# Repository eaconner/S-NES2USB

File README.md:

# (S)NES2USB

Upgrade your NES or SNES controller to USB. Can be put inside the controller, or build real NES/SNES ports onto your computer. Works with standard controllers (original, Max, dogbone, Advantage, etc), does not work with peripherals (Zapper, FourScore, etc).
[OSHPark](https://oshpark.com/shared_projects/MCnz0W9w)  |  [DigiKey BOM](https://www.digikey.com/BOM/Create/CreateSharedBom?bomId=7739089)

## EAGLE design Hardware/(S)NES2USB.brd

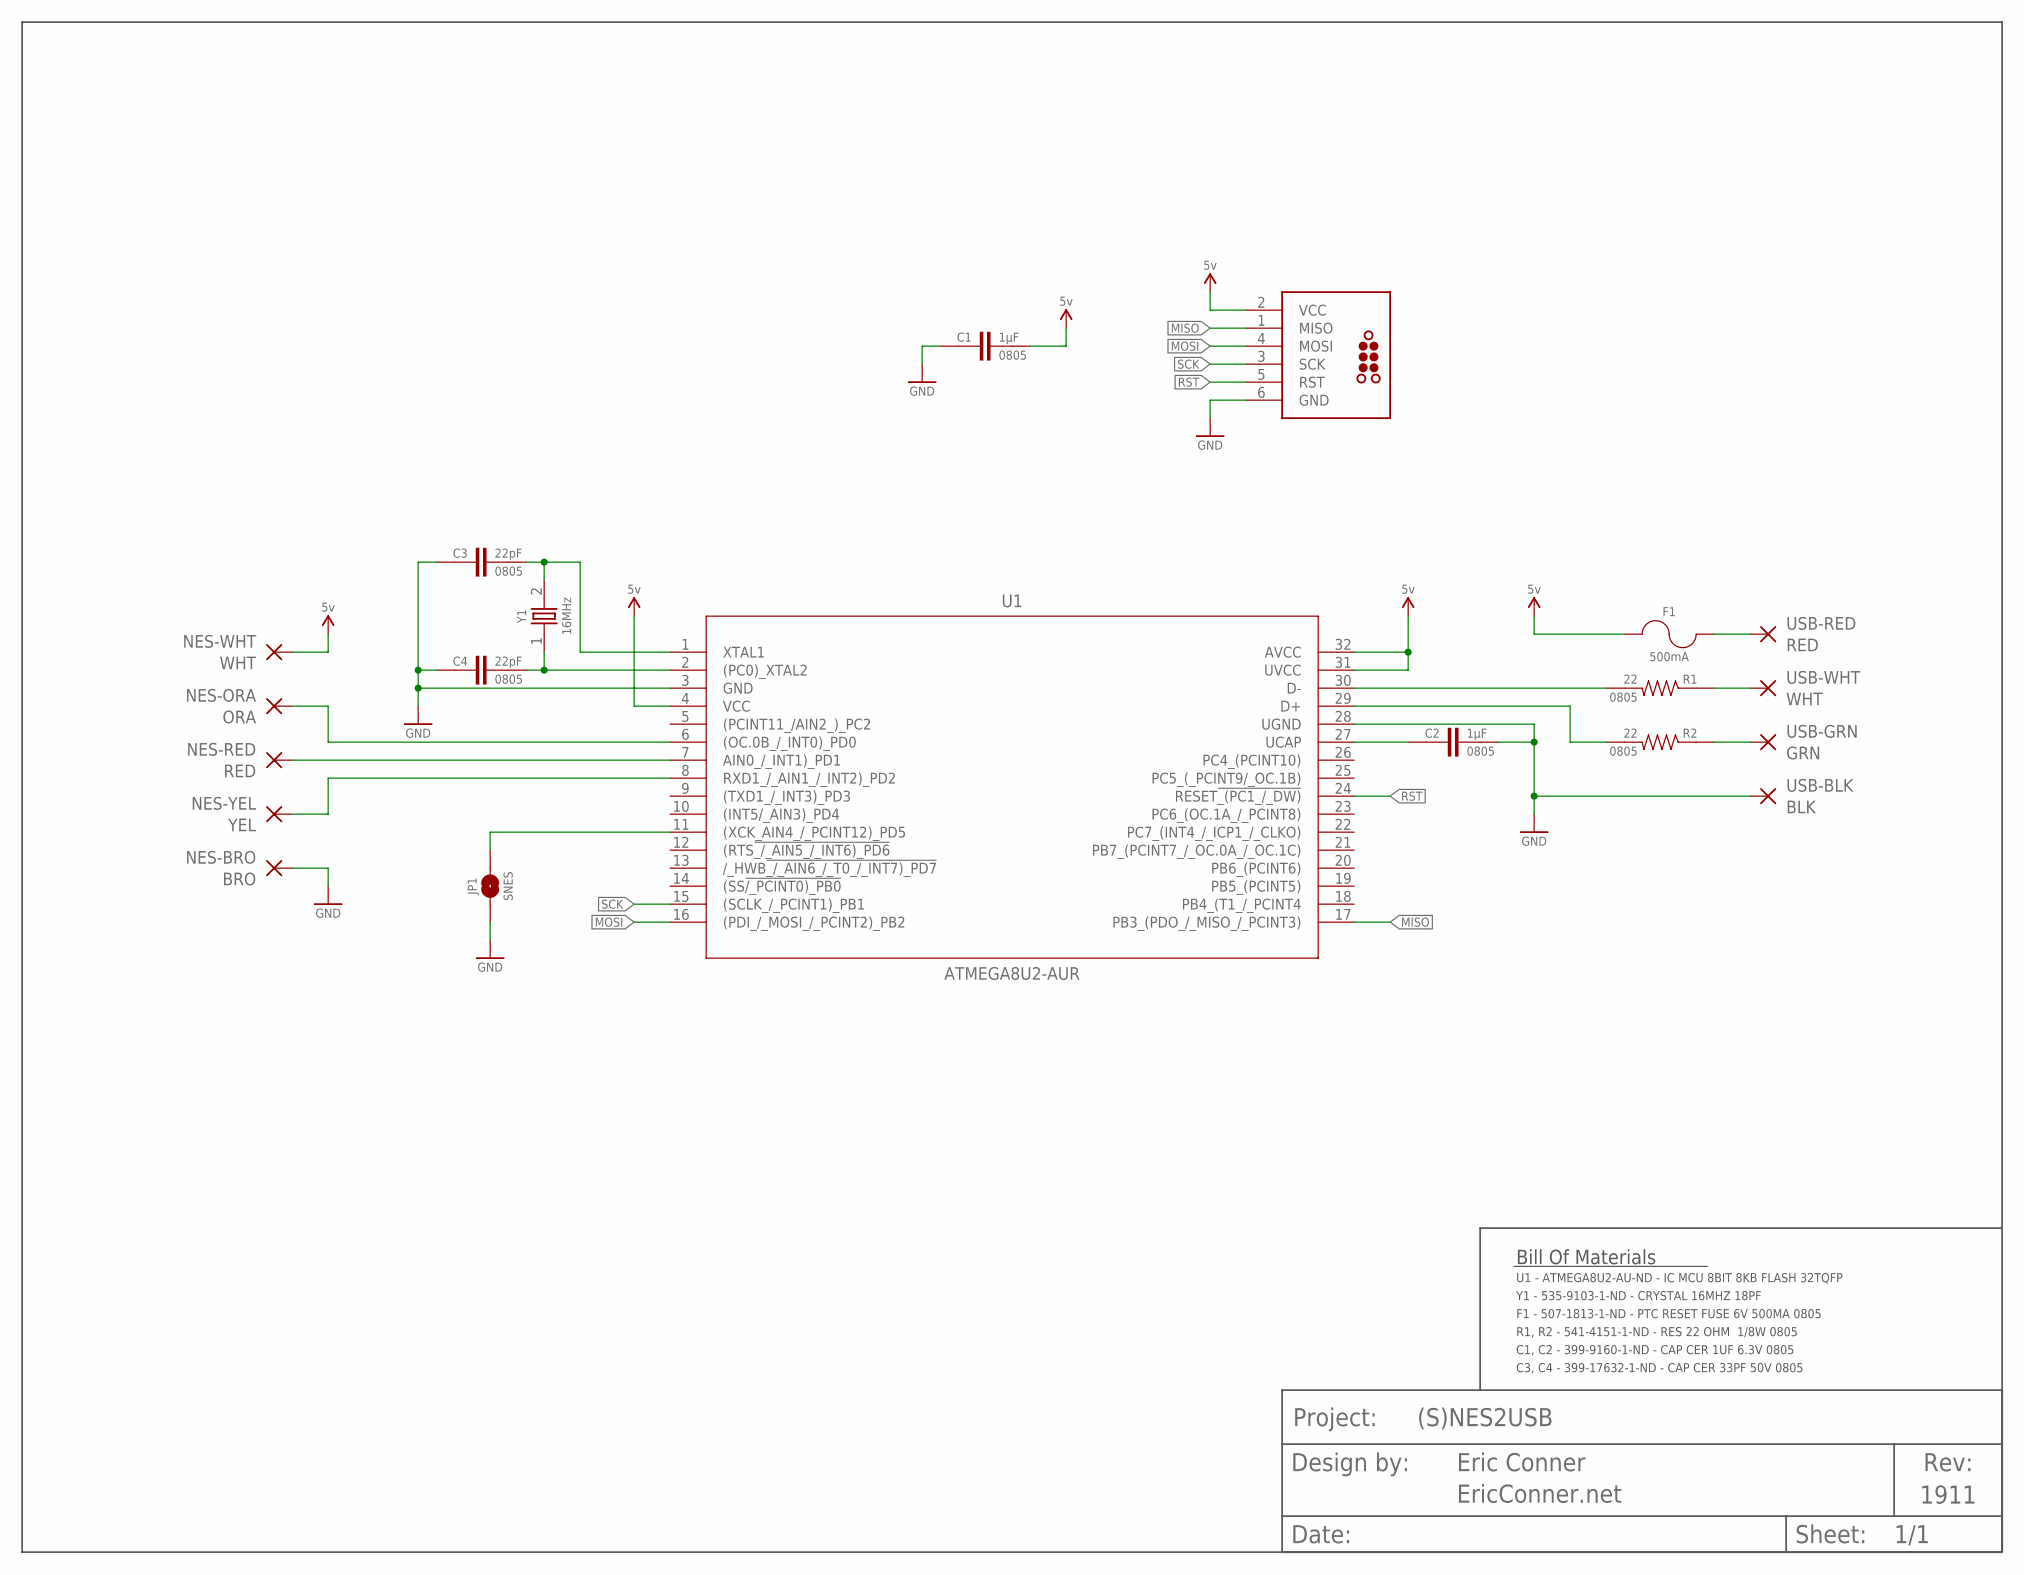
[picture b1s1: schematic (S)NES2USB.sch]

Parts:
BORDER1: BORDER_LETTER-MINIMAL; MINIMAL_LOGO
C1, C2: 1µF; 0805
C3, C4: 22pF; 0805
F1: 500mA; 0805
J1: TC2030
JP1: SNES; SMT-JUMPER_2_NO_SILK
NES-BRO: BRO; SMD1,27-2,54
NES-ORA: ORA; SMD1,27-2,54
NES-RED: RED; SMD1,27-2,54
NES-WHT: WHT; SMD1,27-2,54
NES-YEL: YEL; SMD1,27-2,54
R1, R2: 22; 0805
U1: ATMEGA8U2-AUR; TQFP32
USB-BLK: BLK; SMD1,27-2,54
USB-GRN: GRN; SMD1,27-2,54
USB-RED: RED; SMD1,27-2,54
USB-WHT: WHT; SMD1,27-2,54
Y1: 16MHz; XTAL500X320X130N

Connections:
3V3: C2.1, U1.27 (UCAP)
CLOCK: NES-RED.1, U1.7 (AIN0_/_INT1)_PD1)
D+: R2.2, U1.29 (D+)
D-: R1.2, U1.30 (D-)
DATA: NES-YEL.1, U1.8 (RXD1_/_AIN1_/_INT2)_PD2)
GND: C1.1, C2.2, C3.1, C4.1, J1.6 (GND), JP1.1, NES-BRO.1, U1.3 (GND), U1.28 (UGND), USB-BLK.1
LATCH: NES-ORA.1, U1.6 ((OC.0B_/_INT0)_PD0)
MISO: J1.1 (MISO), U1.17 (PB3_(PDO_/_MISO_/_PCINT3))
MOSI: J1.4 (MOSI), U1.16 ((PDI_/_MOSI_/_PCINT2)_PB2)
RST: J1.5 (RST), U1.24 (RESET!_(PC1_/_DW))
SCK: J1.3 (SCK), U1.15 ((SCLK_/_PCINT1)_PB1)
SNES: JP1.2, U1.11 ((XCK_AIN4_/_PCINT12)_PD5)
USB_5V: F1.1, USB-RED.1
USB_D+: R2.1, USB-GRN.1
USB_D-: R1.1, USB-WHT.1
VCC: C1.2, F1.2, J1.2 (VCC), NES-WHT.1, U1.4 (VCC), U1.31 (UVCC), U1.32 (AVCC)
XTAL1: C4.2, U1.2 ((PC0)_XTAL2), Y1.1
XTAL2: C3.2, U1.1 (XTAL1), Y1.2

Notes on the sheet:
Bill Of Materials
U1 - ATMEGA8U2-AU-ND - IC MCU 8BIT 8KB FLASH 32TQFP
Y1 - 535-9103-1-ND - CRYSTAL 16MHZ 18PF
F1 - 507-1813-1-ND - PTC RESET FUSE 6V 500MA 0805
R1, R2 - 541-4151-1-ND - RES 22 OHM 1/8W 0805
C1, C2 - 399-9160-1-ND - CAP CER 1UF 6.3V 0805
C3, C4 - 399-17632-1-ND - CAP CER 33PF 50V 0805

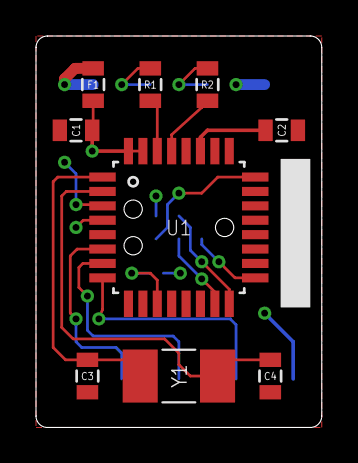
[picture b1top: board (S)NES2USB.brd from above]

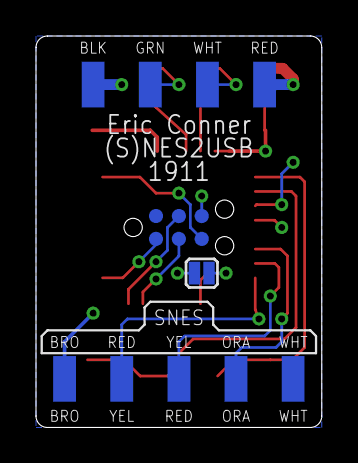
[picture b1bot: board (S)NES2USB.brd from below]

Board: 2 copper layers, 15.9 x 21.7 mm, 21 parts (12 on the bottom side), 18 nets.

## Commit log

2019-11-16 Inital Commit
2019-11-16 Update README.md
    Added OSHPark and DigiKey links
2019-11-16 Update README.md
    Fixed DigiKey link
2019-11-16 Update README.md
    Added Images

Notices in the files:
parts and their libraries:
ECA-Connectors: ©2009 ROFA.cz - modified and updated by Robert Darlington ‹rdarlington@gmail.com›
